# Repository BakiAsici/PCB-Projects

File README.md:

<h2>ESP32-S3-WROOM-1 V1.1 — Custom PCB - Baki Asici</h2>

<p>
  <strong>Updated from V1.0 with improved routing, GPIO reassignment, and antenna layout adjustments.</strong>
</p>

<p>
  A custom-designed ESP32-S3 board featuring onboard I²C sensors, GPIO breakout headers, and full custom routing.  
  Designed in KiCad 9, fabricated by JLCPCB, and hand-assembled using hot air, hotplate, and soldering iron.
</p>

<h3>Overview</h3>

<ul>
  <li>Revision: Rev 1.1</li>
  <li>Designed in: KiCad 9</li>
  <li>Fabricated by: JLCPCB</li>
  <li>Assembly: Hand soldered (Hotplate, Hot Air, Soldering Iron)</li>
</ul>

<h3>Features</h3>

<ul>
  <li>ESP32-S3-WROOM-1 Module</li>
  <li>I²C-connected STMicroelectronics LIS2MDL magnetometer and Bosch Sensortec BME280 environmental sensor (Temperature, Humidity, Pressure)</li>
  <li>GPIO header breakout</li>
  <li>USB Programming and Monitoring</li>
  <li>WiFi and Bluetooth Capabilities</li>
</ul>

<h3>Noted Improvements from Rev 1.0</h3>
<ul>
  <li>Removed top mounting points to improve WiFi and Bluetooth performance, as recommended by the ESP32-S3-WROOM-1 datasheet</li>
  <li>Test LED (marked D1) was originally wired to a strapping pin (GPIO45), which caused unpredictable behaviour. It has now been rewired to a different GPIO</li>
  <li>Completed Custom Bosch BME280 I2C driver in the esp-idf framework. Reading from registers and applying Boch's calibration code</li>
  <li>Improved overall routing</li>
  <li>Followed ESP32-S3-WROOM-1 datasheet more closely regarding antenna clearance and placement</li>
</ul>
<p>It should be noted that IO numbering on back side of pcb may not fully correspond to what the actual pins are. Check schematic.</p>
<h3>Images</h3>
<div>
PCB 3D Renders
<div align="center">  </div>
<div align="center"> </div>

PCB Photos
<div align="center">  </div>
<div align="center"> </div>

Layer Stackup
<div  align="center"> </div>
F.Cu (Front Copper)	
<div  align="center"> </div>
In1.Cu (GND)	
<div  align="center"> </div>
In2.Cu (3V3)	
<div align="center"> </div>
B.Cu (Back Copper)

<h2>ESP32-S3-WROOM-1 V1.0 — Custom PCB</h2>

<p>
  A custom-designed ESP32-S3 board featuring onboard I²C sensors, GPIO breakout headers, and full custom routing.  
  Designed in KiCad 9, fabricated by JLCPCB, and hand-assembled using hot air, hotplate, and soldering iron.
</p>

<h3>Overview</h3>

  <ul>
  <li>Revision: Rev 1.0</li>
  <li>Designed in: KiCad 9</li>
  <li>Fabricated by: JLCPCB</li>
  <li>Assembly: Hand soldered (Hotplate, Hot Air, Soldering Iron)</li>
</ul>

<h3>Features</h3>

<ul>
  <li>ESP32-S3-WROOM-1 Module</li>
  <li>I²C-connected STMicroelectronics LIS2MDL magnetometer and Bosch Sensortec BME280 environmental sensor(Temperature, Humidity, Pressure)</li>
  <li>Sensor libraries used to test functionality with custom drivers in the works</li>
  <li>GPIO header breakout</li>
  <li>USB Programming and Monitoring</li>
  <li>Wifi and Bluetooth Capabilities</li>
</ul>

<h3>Noted Improvements for next revision</h3>
<ul>
  <li>Remove top mounting points to increase Wifi and Bluetooth performance, as recommemnded by the ESP32-S3-WROOM-1 datasheet</li>
  <li>Test led (Marked D1) was wired using a strapping pin GPIO45 and had to be left of the board to ensure predictable behaviour. Rewire led to a new GPIO</li>
  <li>Improve overall routing</li>
  <li>It should be noted that the current limiting resstor for the power indicator led was changed to 180ohms. I am unsure if it will work with the original 1Kohm</li>
</ul>

<h3>Images</h3>
<div >
PCB 3D Renders
<div align="center">  </div>
<div align="center"> </div>

PCB Photos
<div align="center">  </div>
<div align="center"> </div>

Layer Stackup
<div  align="center"> </div>
F.Cu (Front Copper)	
<div  align="center"> </div>
In1.Cu (GND)	
<div  align="center"> </div>
In2.Cu (3V3)	
<div  align="center"> </div>
B.Cu (Back Copper)

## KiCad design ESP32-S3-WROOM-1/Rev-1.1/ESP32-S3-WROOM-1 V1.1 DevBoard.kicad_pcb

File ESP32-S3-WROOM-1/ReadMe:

This is a ESP32-S3 based embedded prototyping and iot pcb I have made custom. I desgined it in Kicad 9 and manufactured it with JLCPCB. All Schematics and PCB files for each revisions are listed here

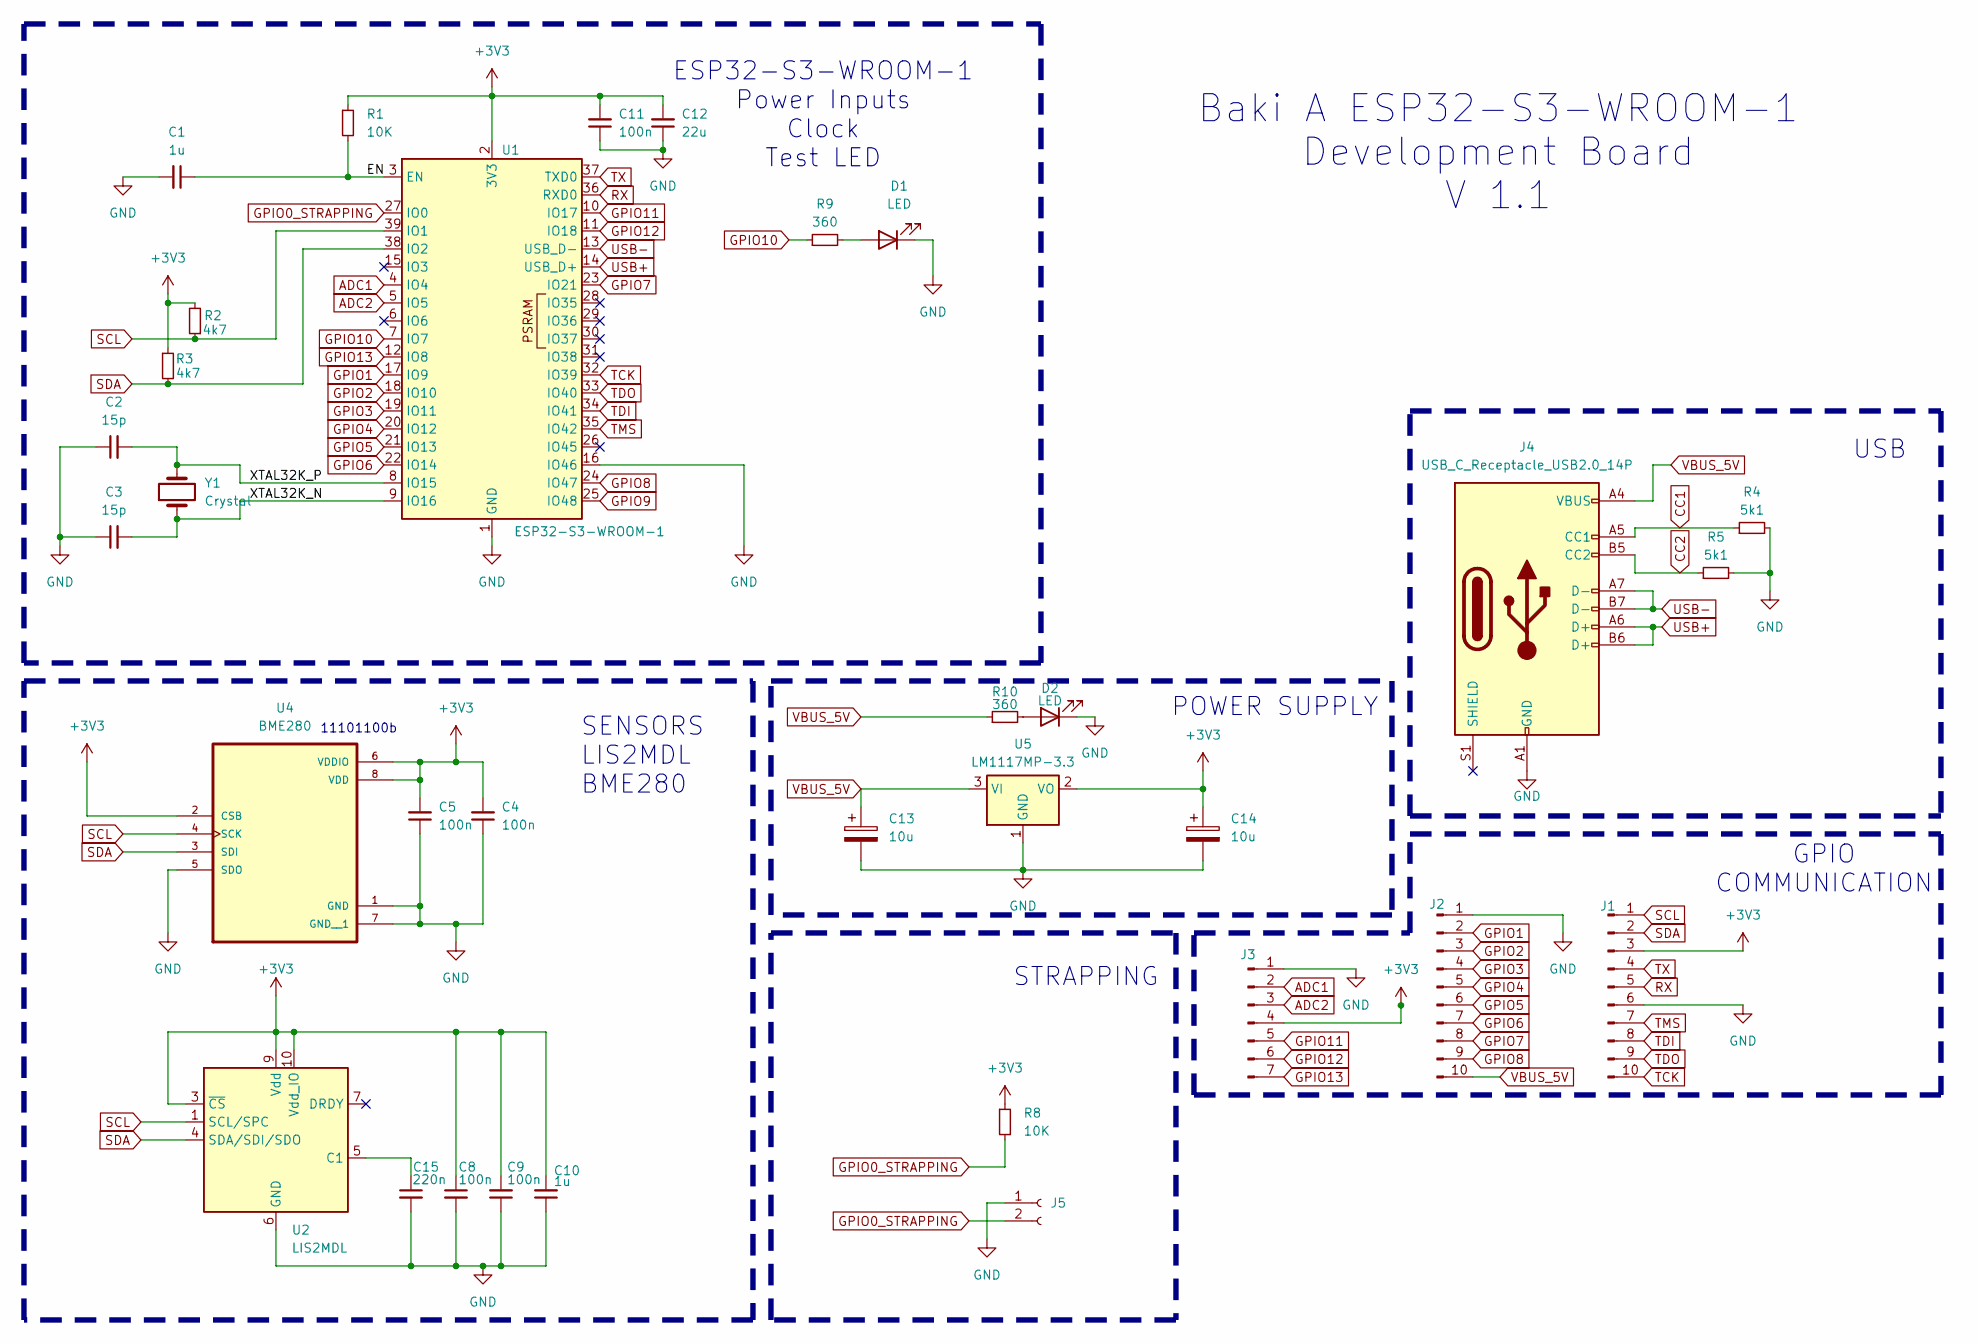
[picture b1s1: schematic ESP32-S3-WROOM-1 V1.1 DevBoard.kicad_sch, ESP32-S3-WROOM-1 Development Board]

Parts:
C1, C10: 1u; C_1206_3216Metric
C2, C3: 15p; C_1206_3216Metric
C4, C5, C8, C9, C11: 100n; C_1206_3216Metric
C12: 22u; C_1206_3216Metric
C13, C14: 10u; CP_EIA-3216-18_Kemet-A
C15: 220n; C_1206_3216Metric
D1, D2: LED; LED_1206_3216Metric
J1: Comms; PinHeader_1x10_P2.54mm_Vertical
J2: Conn_01x10_Pin; PinHeader_1x10_P2.54mm_Vertical
J3: Conn_01x07_Pin; PinHeader_1x07_P2.54mm_Vertical
J4: USB_C_Receptacle_USB2.0_14P; USB_C_Receptacle_HRO_TYPE-C-31-M-12
J5: Conn_01x02_Socket; PinSocket_1x02_P2.54mm_Vertical
R1, R8: 10K; R_1206_3216Metric
R2, R3: 4k7; R_1206_3216Metric
R4, R5: 5k1; R_1206_3216Metric
R9, R10: 360; R_1206_3216Metric
U1: ESP32-S3-WROOM-1
U2: LIS2MDL; LGA-12_2x2mm_P0.5mm
U4: BME280; PSON65P250X250X100-8N
U5: LM1117MP-3.3; SOT-223-3_TabPin2
Y1: Crystal; Crystal_SMD_3215-2Pin_3.2x1.5mm

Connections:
+3V3: C4.2, C5.2, C8.1, C9.2, C10.2, C11.2, C12.2, C14.1, J1.3, J3.4, R1.1, R2.2, R3.1, R8.1, U1.2 (3V3), U2.3 (~CS), U2.9 (Vdd), U2.10 (Vdd_IO), U4.2 (CSB), U4.6 (VDDIO), U4.8 (VDD), U5.2 (VO)
/EN: C1.1, R1.2, U1.3 (EN)
/XTAL32K_N: C3.2, U1.9 (IO16), Y1.1
/XTAL32K_P: C2.2, U1.8 (IO15), Y1.2
ADC1: J3.2, U1.4 (IO4)
ADC2: J3.3, U1.5 (IO5)
CC1: J4.A5 (CC1), R4.1
CC2: J4.B5 (CC2), R5.1
GND: C1.2, C2.1, C3.1, C4.1, C5.1, C8.2, C9.1, C10.1, C11.1, C12.1, C13.2, C14.2, C15.2, D1.1 (K), D2.1 (K), J1.6, J2.1, J3.1, J4.A1 (GND), J4.A12 (GND), J4.B1 (GND), J4.B12 (GND), J5.1, R4.2, R5.2, U1.1 (GND), U1.16 (IO46), U1.40 (GND), U1.41 (GND), U2.6 (GND), U2.8 (GND), U4.1 (GND), U4.5 (SDO), U4.7 (GND__1), U5.1 (GND)
GPIO0_STRAPPING: J5.2, R8.2, U1.27 (IO0)
GPIO1: J2.2, U1.17 (IO9)
GPIO2: J2.3, U1.18 (IO10)
GPIO3: J2.4, U1.19 (IO11)
GPIO4: J2.5, U1.20 (IO12)
GPIO5: J2.6, U1.21 (IO13)
GPIO6: J2.7, U1.22 (IO14)
GPIO7: J2.8, U1.23 (IO21)
GPIO8: J2.9, U1.24 (IO47)
GPIO9: R9.1, U1.7 (IO7)
GPIO10: J3.5, U1.10 (IO17)
GPIO11: J3.6, U1.11 (IO18)
GPIO12: J3.7, U1.12 (IO8)
unnamed: D1.2 (A), R9.2
unnamed: D2.2 (A), R10.2
unnamed: C15.1, U2.5 (C1)
RX: J1.5, U1.36 (RXD0)
SCL: J1.1, R2.1, U1.39 (IO1), U2.1 (SCL/SPC), U4.4 (SCK)
SDA: J1.2, R3.2, U1.38 (IO2), U2.4 (SDA/SDI/SDO), U4.3 (SDI)
TCK: J1.10, U1.32 (IO39)
TDI: J1.8, U1.34 (IO41)
TDO: J1.9, U1.33 (IO40)
TMS: J1.7, U1.35 (IO42)
TX: J1.4, U1.37 (TXD0)
USB+: J4.A6 (D+), J4.B6 (D+), U1.14 (USB_D+)
USB-: J4.A7 (D-), J4.B7 (D-), U1.13 (USB_D-)
VBUS_5V: C13.1, J2.10, J4.A4 (VBUS), J4.A9 (VBUS), J4.B4 (VBUS), J4.B9 (VBUS), R10.1, U5.3 (VI)

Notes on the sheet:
Baki A ESP32-S3-WROOM-1 Development Board V 1.1
USB
11101100b
POWER SUPPLY
GPIO COMMUNICATION
SENSORS LIS2MDL BME280
STRAPPING
ESP32-S3-WROOM-1 Power Inputs Clock Test LED

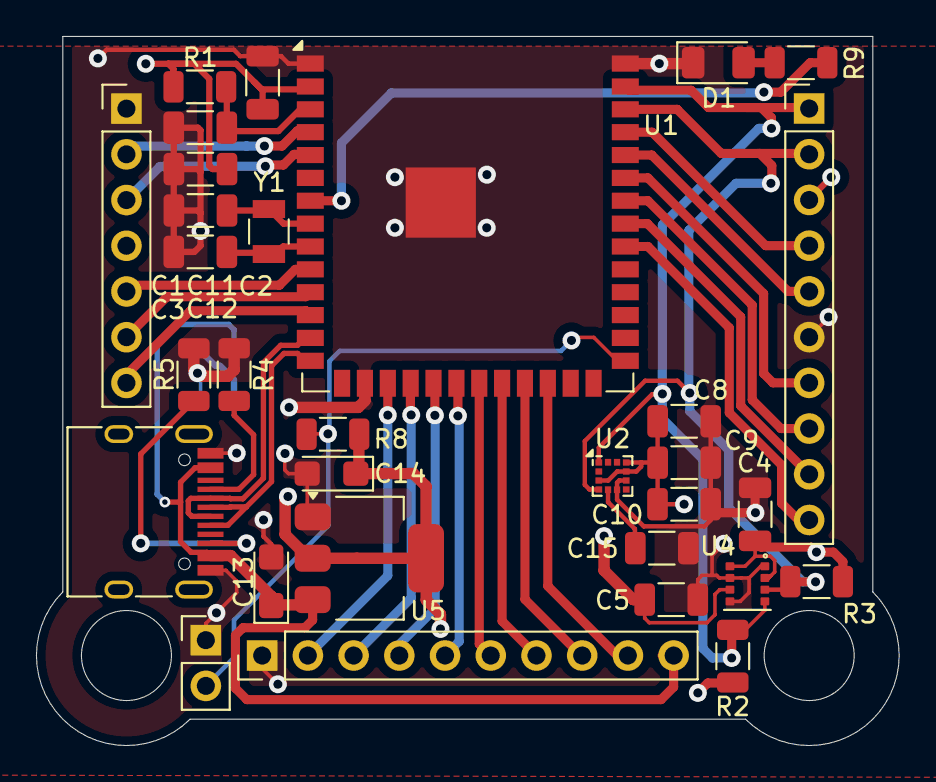
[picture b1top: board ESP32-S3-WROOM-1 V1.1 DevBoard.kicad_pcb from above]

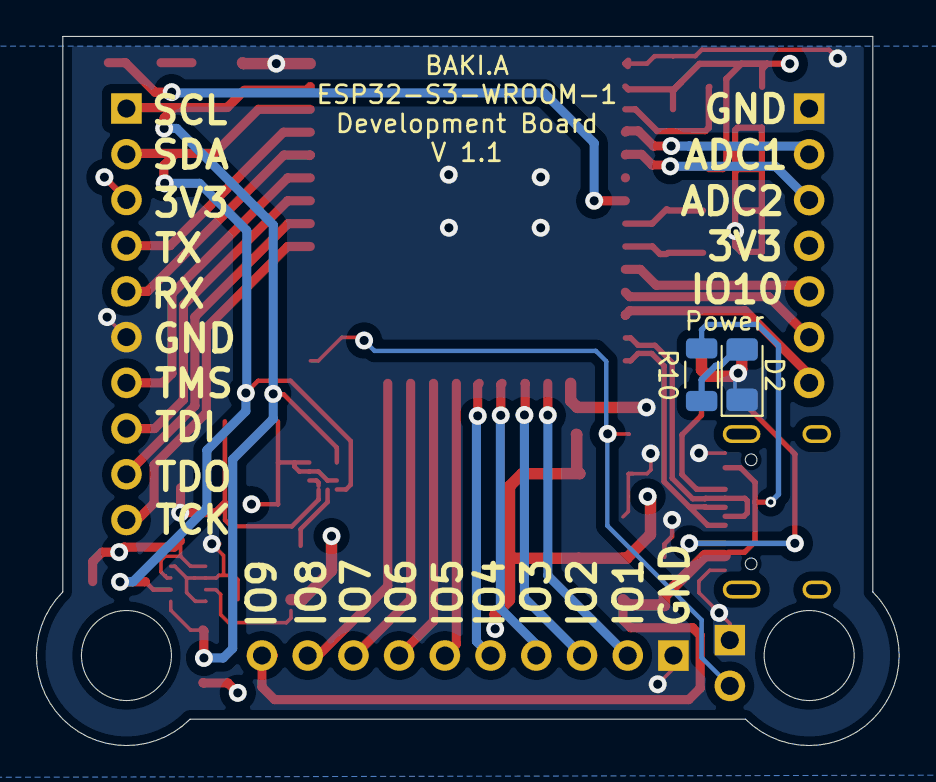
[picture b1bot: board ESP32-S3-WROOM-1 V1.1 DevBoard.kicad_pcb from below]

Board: 4 copper layers, 47.9 x 39.4 mm, 33 parts (2 on the bottom side), 36 nets.

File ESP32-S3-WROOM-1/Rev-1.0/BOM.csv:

"Reference","Qty","Value","DNP","Exclude from BOM","Exclude from Board","Footprint","Datasheet"
"C1,C10","2","1u","","","","Capacitor_SMD:C_1206_3216Metric","~"
"C2,C3","2","15p","","","","Capacitor_SMD:C_1206_3216Metric","~"
"C4,C5,C8,C9,C11","5","100n","","","","Capacitor_SMD:C_1206_3216Metric","~"
"C12","1","22u","","","","Capacitor_SMD:C_1206_3216Metric","~"
"C13,C14","2","10u","","","","Capacitor_Tantalum_SMD:CP_EIA-3216-18_Kemet-A","~"
"C15","1","220n","","","","Capacitor_SMD:C_1206_3216Metric","~"
"D1,D2","2","LED","","","","LED_SMD:LED_1206_3216Metric","~"
"J1","1","Comms","","","","Connector_PinHeader_2.54mm:PinHeader_1x10_P2.54mm_Vertical","~"
"J2","1","Conn_01x10_Pin","","","","Connector_PinHeader_2.54mm:PinHeader_1x10_P2.54mm_Vertical","~"
"J3","1","Conn_01x07_Pin","","","","Connector_PinHeader_2.54mm:PinHeader_1x07_P2.54mm_Vertical","~"
"J4","1","USB_C_Receptacle_USB2.0_14P","","","","Connector_USB:USB_C_Receptacle_HRO_TYPE-C-31-M-12","https://www.usb.org/sites/default/files/documents/usb_type-c.zip"
"J5","1","Conn_01x02_Socket","","","","Connector_PinSocket_2.54mm:PinSocket_1x02_P2.54mm_Vertical","~"
"R1,R8","2","10K","","","","Resistor_SMD:R_1206_3216Metric","~"
"R2,R3","2","4k7","","","","Resistor_SMD:R_1206_3216Metric","~"
"R4,R5","2","5k1","","","","Resistor_SMD:R_1206_3216Metric","~"
"R9,R10","2","1K","","","","Resistor_SMD:R_1206_3216Metric","~"
"U1","1","ESP32-S3-WROOM-1","","","","RF_Module:ESP32-S3-WROOM-1","https://www.espressif.com/sites/default/files/documentation/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"
"U2","1","LIS2MDL","","","","Package_LGA:LGA-12_2x2mm_P0.5mm","https://www.st.com/resource/en/datasheet/lis2mdl.pdf"
"U4","1","BME280","","","","BME280:PSON65P250X250X100-8N",""
"U5","1","LM1117MP-3.3","","","","Package_TO_SOT_SMD:SOT-223-3_TabPin2","http://www.ti.com/lit/ds/symlink/lm1117.pdf"
"Y1","1","Crystal","","","","Crystal:Crystal_SMD_3215-2Pin_3.2x1.5mm","~"

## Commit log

2025-06-02 Create EPS32-S3-WROOM-1-N8R2 Project
2025-06-02 Update EPS32-S3-WROOM-1-N8R2 Project
2025-06-27 Folder name change and general formatting
2025-06-27 Create testimage
2025-06-27 delete
2025-06-27 Create test
2025-06-27 Create testimg
2025-06-27 new schematic pdf
2025-06-27 Create LICENSE
2025-06-27 failed
2025-06-27 Fixing Typo
2025-07-02 added gerber
2025-07-02 added bom
2025-07-04 readme=
2025-07-05 readme
